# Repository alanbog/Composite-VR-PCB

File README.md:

# Composite-VR-PCB

This repository contains the hardware design of a controller board for CRT-based VR headset. The circuit contains an AMD Spartan 7 FPGA which splits the incoming HDMI video into separate luma only (black-and-white) NTSC composite video signals for the left and right eye. It also contains an RP2040 microcontroller which serves two purposes:

1. Act as a JTAG programmer for the FPGA using [xvc-pico](https://github.com/kholia/xvc-pico)
2. Transmit 3-DOF tracking data back to a PC using the on-board IMU (based on [Relativty](https://github.com/relativty/Relativty)).

The board also contains a USB hub and a USB C port intended to be connected to a Vive Tracker. When a Vive tracker is connected and SteamVR settings are configured to use the Vive Tracker to [override the default tracking](https://github.com/ValveSoftware/openvr/wiki/TrackingOverrides), the onboard IMU  tracking will not be used, and the RP2040 will only serve to let SteamVR know that the headset is connected. 

The board is the same dimensions and has the same mounting hole placement as a Raspberry Pi Zero.

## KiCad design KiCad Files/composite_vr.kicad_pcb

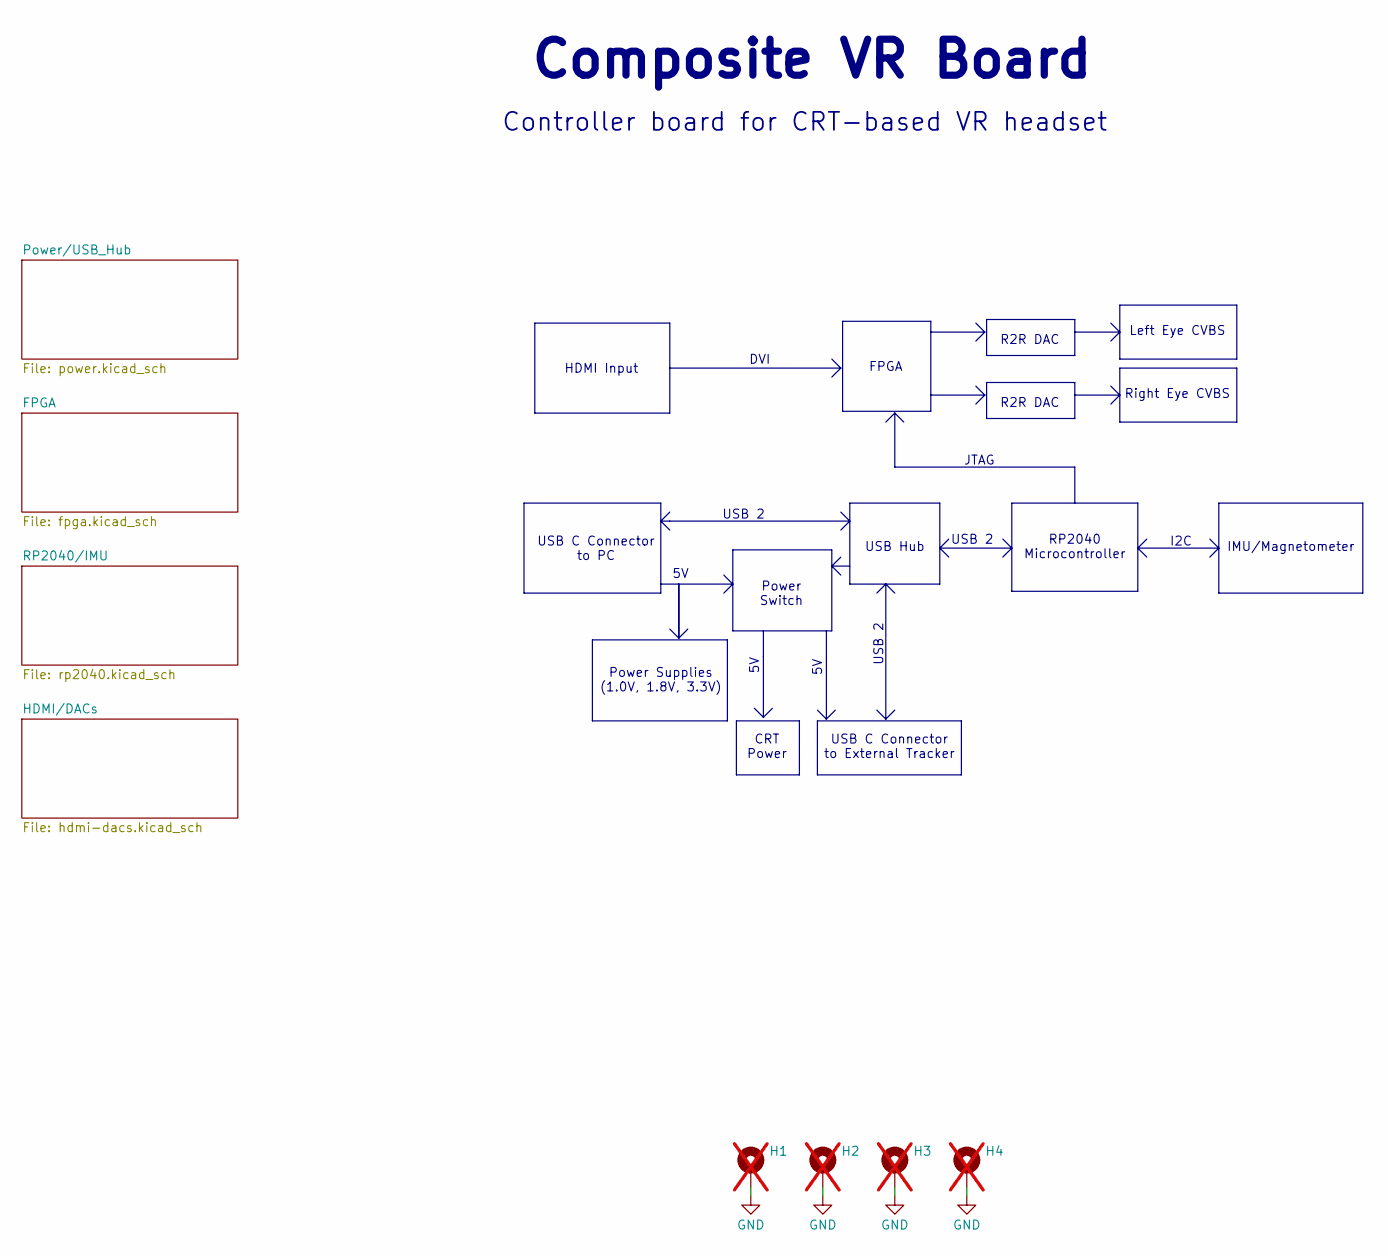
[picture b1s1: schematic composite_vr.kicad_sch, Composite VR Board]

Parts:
H1, H2, H3, H4: MountingHole_Pad; MountingHole_2.7mm_M2.5_DIN965_Pad; not fitted

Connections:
GND: H1.1, H2.1, H3.1, H4.1; also elsewhere on the board

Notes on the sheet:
USB 2
USB C Connector to External Tracker
Controller board for CRT-based VR headset
R2R DAC
FPGA
CRT Power
USB C Connector to PC
IMU/Magnetometer
Left Eye CVBS
USB Hub
Power Switch
Power Supplies (1.0V, 1.8V, 3.3V)
I2C
RP2040 Microcontroller
Right Eye CVBS
Composite VR Board
HDMI Input
DVI
JTAG

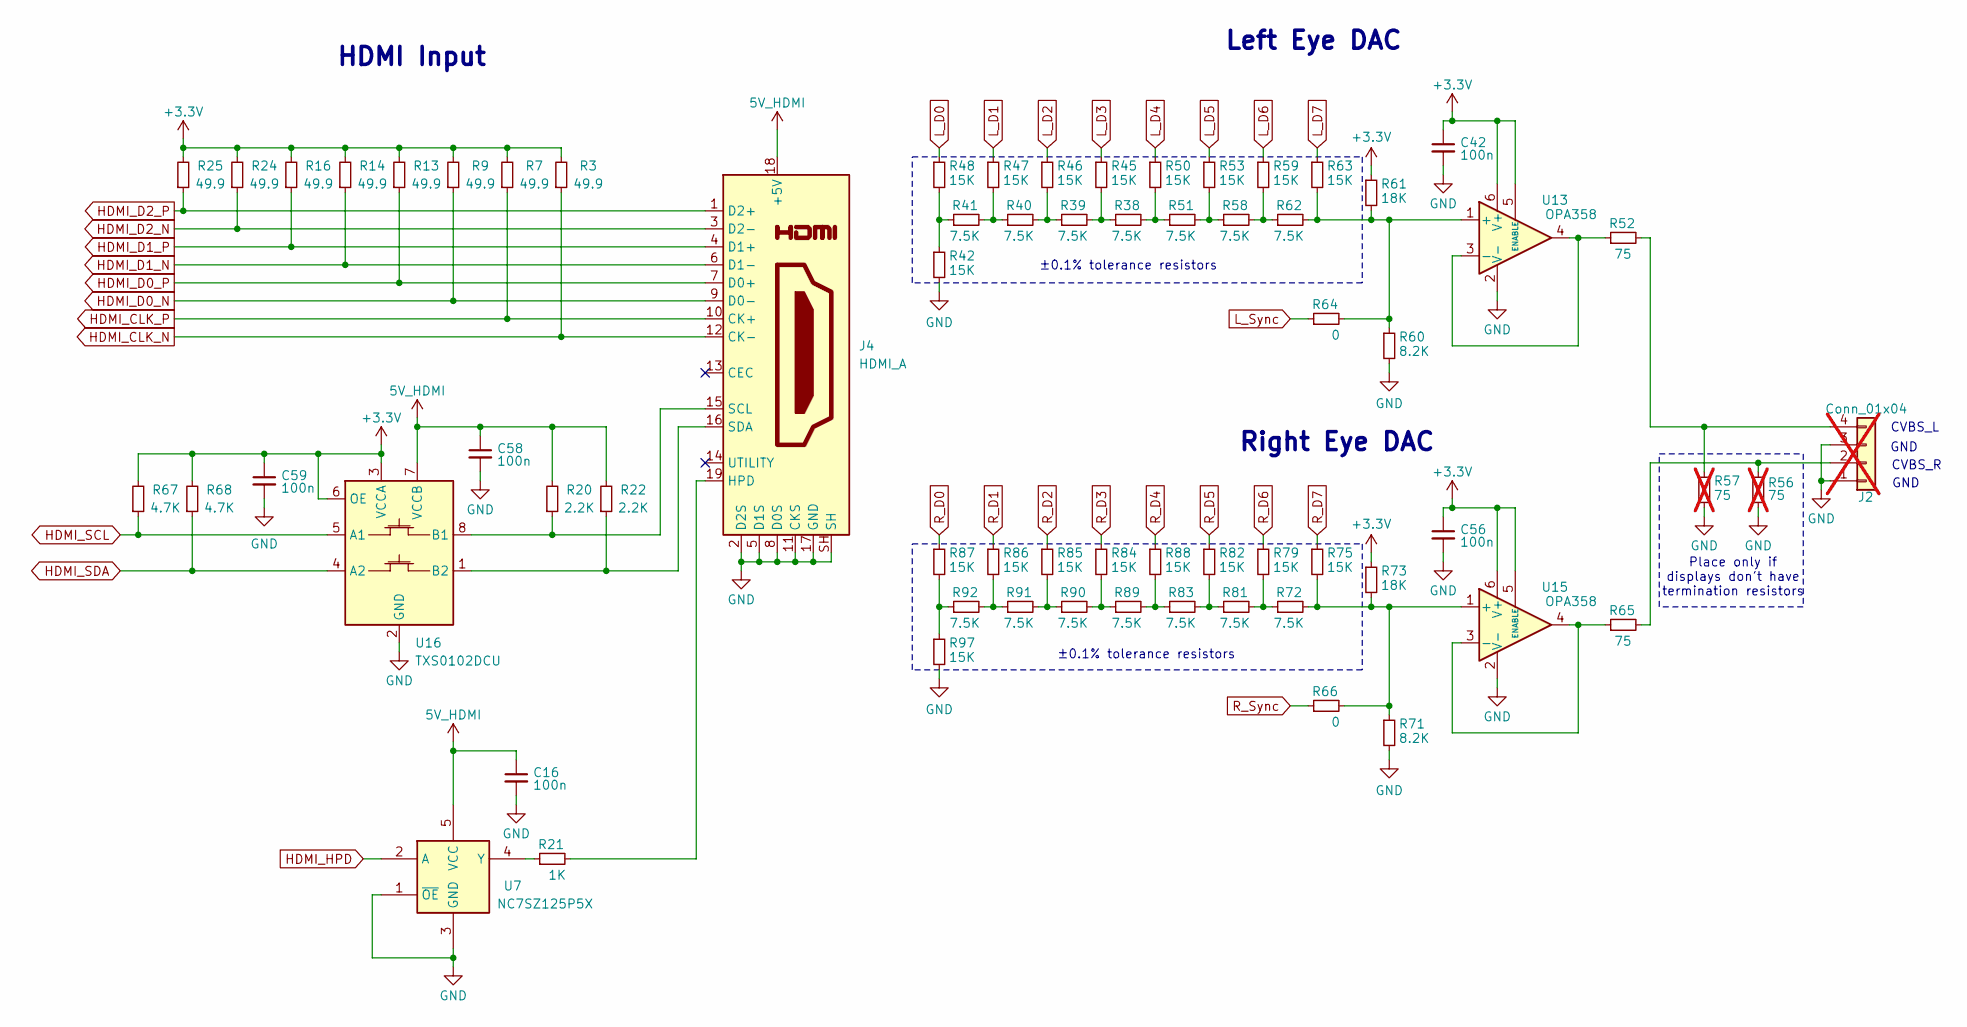
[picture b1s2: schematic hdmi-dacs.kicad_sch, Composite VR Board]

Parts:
C16, C42, C56, C58, C59: 100n; C_0402; Rating 16V; Tolerance 10%; Mfg PN CL05B104KO5NNNC; JLCPCB C1525
J2: Conn_01x04; PinHeader_1x04_P2.54mm_Vertical; not fitted
J4: HDMI_A; HDMI_A_Molex_208658-1001_Horizontal; Mfg PN HDMI-001S; JLCPCB C720616
R3, R7, R9, R13, R14, R16, R24, R25: 49.9; R_0402; Rating 62.5mW; Tolerance 1%; Mfg PN 0402WGF499JTCE; JLCPCB C25120
R20, R22: 2.2K; R_0402; Rating 62.5mW; Tolerance 1%; Mfg PN 0402WGF2201TCE; JLCPCB C25879
R21: 1K; R_0402; Rating 62.5mW; Tolerance 1%; Mfg PN 0402WGF1001TCE; JLCPCB C11702
R38, R39, R40, R41, R51, R58, R62, R72, R81, R83, R89, R90, R91, R92: 7.5K; R_0402; Rating 62.5mW; Tolerance 0.1%; Mfg PN TC0225B7501TCC; JLCPCB C28566374
R42, R45, R46, R47, R48, R50, R53, R59, R63, R75, R79, R82, R84, R85, R86, R87, R88, R97: 15K; R_0402; Rating 62.5mW; Tolerance 0.1%; Mfg PN TC02G1502BT; JLCPCB C20627044
R52, R65: 75; R_0402; Rating 62.5mW; Tolerance 1%; Mfg PN 0402WGF750JTCE; JLCPCB C25133
R56, R57: 75; R_0402; Rating 62.5mW; Tolerance 1%; Mfg PN 0402WGF750JTCE; JLCPCB C25133; not fitted
R60, R71: 8.2K; R_0402; Rating 62.5mW; Tolerance 1%; Mfg PN 0402WGF8201TCE; JLCPCB C25924
R61, R73: 18K; R_0402; Rating 62.5mW; Tolerance 1%; Mfg PN 0402WGF1802TCE; JLCPCB C25762
R64, R66: 0; R_0402; Rating 62.5mW; Tolerance 1%; Mfg PN 0402WGF0000TCE; JLCPCB C17168
R67, R68: 4.7K; R_0402; Rating 62.5mW; Tolerance 1%; Mfg PN 0402WGF4701TCE; JLCPCB C25900
U7: NC7SZ125P5X; SOT-353_SC-70-5; Mfg PN NC7SZ125P5X; JLCPCB C112084
U13, U15: OPA358; SOT-363_SC-70-6; Mfg PN OPA358AIDCKT; JLCPCB C2057755
U16: TXS0102DCU; VSSOP-8_2.3x2mm_P0.5mm; Mfg PN TXS0102DCUR; JLCPCB C53434

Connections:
5V_HDMI: C16.1, C58.1, J4.18 (+5V), R20.2, R22.2, U7.5 (VCC), U16.7 (VCCB)
+3.3V: C42.1, C56.1, C59.1, R3.2, R7.2, R9.2, R13.2, R14.2, R16.2, R24.2, R25.2, R61.1, R67.2, R68.2, R73.1, U13.5 (ENABLE), U13.6 (V+), U15.5 (ENABLE), U15.6 (V+), U16.3 (VCCA), U16.6 (OE); also elsewhere on the board
GND: C16.2, C42.2, C56.2, C58.2, C59.2, J2.1, J2.3, J4.2 (D2S), J4.5 (D1S), J4.8 (D0S), J4.11 (CKS), J4.17 (GND), J4.SH, R42.2, R56.2, R57.2, R60.2, R71.2, R97.2, U7.1 (~OE), U7.3 (GND), U13.2 (V-), U15.2 (V-), U16.2 (GND); also elsewhere on the board
HDMI_CLK_N: J4.12 (CK-), R3.1; also elsewhere on the board
HDMI_CLK_P: J4.10 (CK+), R7.1; also elsewhere on the board
HDMI_D0_N: J4.9 (D0-), R9.1; also elsewhere on the board
HDMI_D0_P: J4.7 (D0+), R13.1; also elsewhere on the board
HDMI_D1_N: J4.6 (D1-), R14.1; also elsewhere on the board
HDMI_D1_P: J4.4 (D1+), R16.1; also elsewhere on the board
HDMI_D2_N: J4.3 (D2-), R24.1; also elsewhere on the board
HDMI_D2_P: J4.1 (D2+), R25.1; also elsewhere on the board
HDMI_HPD: U7.2 (A); also elsewhere on the board
HDMI_SCL: R67.1, U16.5 (A1); also elsewhere on the board
HDMI_SDA: R68.1, U16.4 (A2); also elsewhere on the board
L_D0: R48.1; also elsewhere on the board
L_D1: R47.1; also elsewhere on the board
L_D2: R46.1; also elsewhere on the board
L_D3: R45.1; also elsewhere on the board
L_D4: R50.1; also elsewhere on the board
L_D5: R53.1; also elsewhere on the board
L_D6: R59.1; also elsewhere on the board
L_D7: R63.1; also elsewhere on the board
L_Sync: R64.1; also elsewhere on the board
unnamed: J2.2, R56.1, R65.2
unnamed: J2.4, R52.2, R57.1
unnamed: J4.19 (HPD), R21.2
unnamed: J4.15 (SCL), R20.1, U16.8 (B1)
unnamed: J4.16 (SDA), R22.1, U16.1 (B2)
unnamed: R38.1, R39.2, R45.2
unnamed: R38.2, R50.2, R51.1
unnamed: R39.1, R40.2, R46.2
unnamed: R40.1, R41.2, R47.2
unnamed: R41.1, R42.1, R48.2
unnamed: R51.2, R53.2, R58.1
unnamed: R58.2, R59.2, R62.1
unnamed: R72.1, R79.2, R81.2
unnamed: R81.1, R82.2, R83.2
unnamed: R83.1, R88.2, R89.2
unnamed: R84.2, R89.1, R90.2
unnamed: R85.2, R90.1, R91.2
unnamed: R86.2, R91.1, R92.2
unnamed: R87.2, R92.1, R97.1
unnamed: R21.1, U7.4 (Y)
unnamed: R60.1, R61.2, R62.2, R63.2, R64.2, U13.1 (+)
unnamed: R52.1, U13.3 (-), U13.4
unnamed: R66.2, R71.1, R72.2, R73.2, R75.2, U15.1 (+)
unnamed: R65.1, U15.3 (-), U15.4
R_D0: R87.1; also elsewhere on the board
R_D1: R86.1; also elsewhere on the board
R_D2: R85.1; also elsewhere on the board
R_D3: R84.1; also elsewhere on the board
R_D4: R88.1; also elsewhere on the board
R_D5: R82.1; also elsewhere on the board
R_D6: R79.1; also elsewhere on the board
R_D7: R75.1; also elsewhere on the board
R_Sync: R66.1; also elsewhere on the board

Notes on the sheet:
CVBS_R
CVBS_L
Right Eye DAC
±0.1% tolerance resistors
Place only if displays don't have termination resistors
GND
Left Eye DAC
HDMI Input

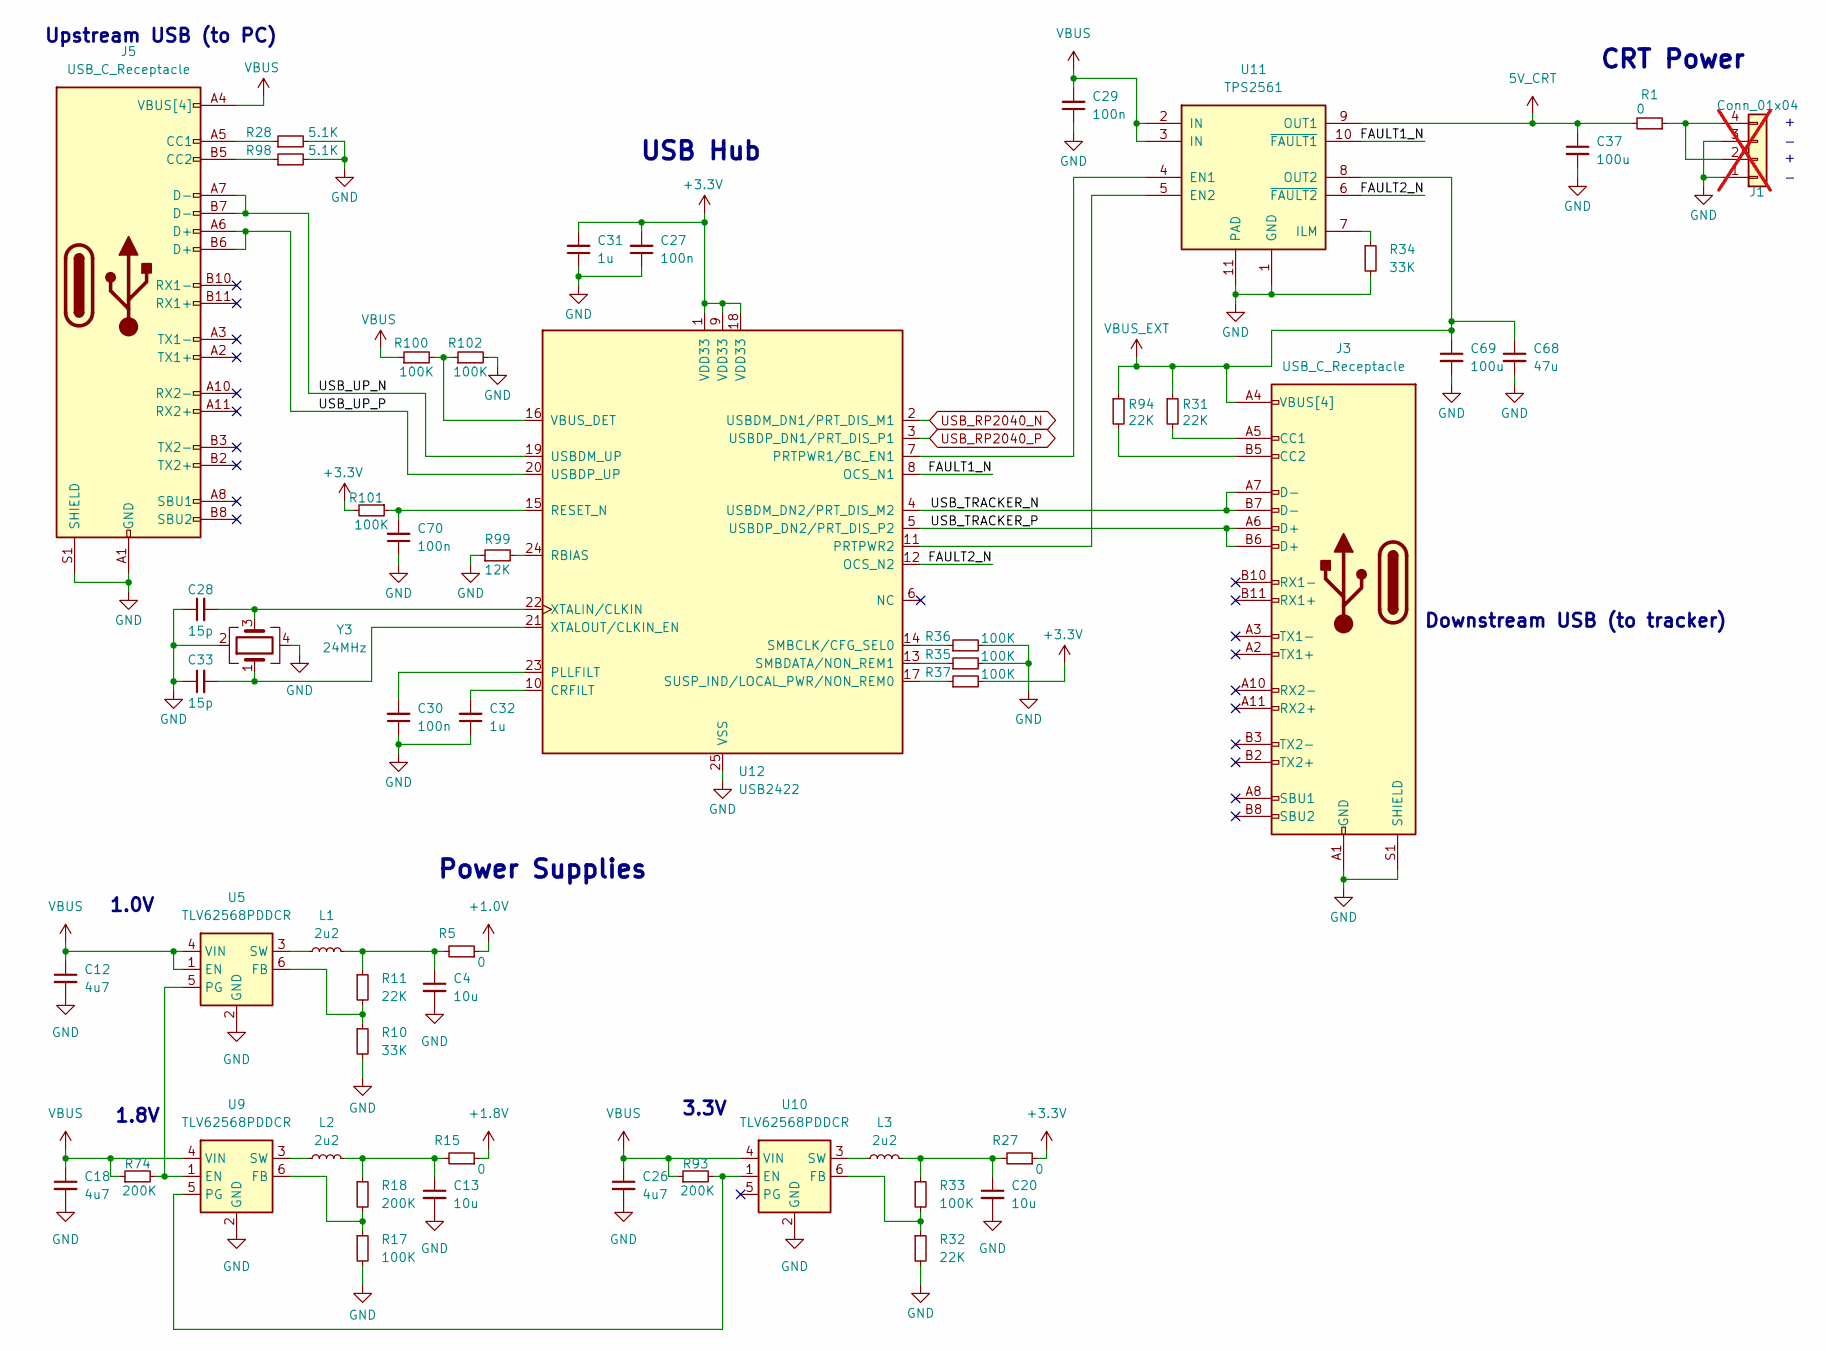
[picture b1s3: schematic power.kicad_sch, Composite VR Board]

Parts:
C4, C13, C20: 10u; C_0603; Rating 10V; Tolerance 10%; Mfg PN CL10A106KP8NNNC; JLCPCB C19702
C12, C18, C26: 4u7; C_0402; Rating 10V; Tolerance 20%; Mfg PN CL05A475MP5NRNC; JLCPCB C23733
C27, C29, C30, C70: 100n; C_0402; Rating 16V; Tolerance 10%; Mfg PN CL05B104KO5NNNC; JLCPCB C1525
C28, C33: 15p; C_0402; Rating 50V; Tolerance 5%; Mfg PN 0402CG150J500NT; JLCPCB C1548
C31, C32: 1u; C_0402; Rating 25V; Tolerance 10%; Mfg PN CL05A105KA5NQNC; JLCPCB C52923
C37, C69: 100u; C_1206; Rating 6.3V; Tolerance 20%; Mfg PN CL31A107MQHNNNE; JLCPCB C15008
C68: 47u; C_0805; Rating 6.3V; Tolerance 20%; Mfg PN CL21A476MQYNNNE; JLCPCB C16780
J1: Conn_01x04; PinHeader_1x04_P2.54mm_Vertical; not fitted
J3, J5: USB_C_Receptacle; USB_C_Receptacle_Molex_105450-0101; Mfg PN 1054500101; JLCPCB C134092
L1, L2, L3: 2u2; L_Taiyo-Yuden_MD-3030; Mfg PN LQH3NPN2R2MJRL; JLCPCB C341775
R1, R5, R15, R27: 0; R_0402; Rating 62.5mW; Tolerance 1%; Mfg PN 0402WGF0000TCE; JLCPCB C17168
R10, R34: 33K; R_0402; Rating 62.5mW; Tolerance 1%; Mfg PN 0402WGF3302TCE; JLCPCB C25779
R11, R31, R32, R94: 22K; R_0402; Rating 62.5mW; Tolerance 1%; Mfg PN 0402WGF2202TCE; JLCPCB C25768
R17, R33, R35, R36, R37, R100, R101, R102: 100K; R_0402; Rating 62.5mW; Tolerance 1%; Mfg PN 0402WGF1003TCE; JLCPCB C25741
R18, R74, R93: 200K; R_0402; Rating 62.5mW; Tolerance 1%; Mfg PN 0402WGF2003TCE; JLCPCB C25764
R28, R98: 5.1K; R_0402; Rating 62.5mW; Tolerance 1%; Mfg PN 0402WGF5101TCE; JLCPCB C25905
R99: 12K; R_0402; Rating 62.5mW; Tolerance 1%; Mfg PN 0402WGF1202TCE; JLCPCB C25752
U5, U9, U10: TLV62568PDDCR; SOT-23-6-small_courtyard; Mfg PN TLV62568PDDCR; JLCPCB C398369
U11: TPS2561; VSON-10-1EP_3x3mm_P0.5mm_EP1.65x2.4mm_ThermalVias; Mfg PN TPS2561DRCR; JLCPCB C140303
U12: USB2422; QFN-24-1EP_4x4mm_P0.5mm_EP2.5x2.5mm; Mfg PN USB2422T/MJ; JLCPCB C622611
Y3: 24MHz; Crystal_SMD_3225-4Pin_3.2x2.5mm; Mfg PN 7U24000E09UCG; JLCPCB C251611

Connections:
5V_CRT: C37.1, R1.2, U11.9 (OUT1)
+1.0V: R5.1; also elsewhere on the board
+1.8V: R15.1; also elsewhere on the board
+3.3V: C27.2, C31.2, R27.1, R37.2, R101.2, U12.1 (VDD33), U12.9 (VDD33), U12.18 (VDD33); also elsewhere on the board
/Power/USB_Hub/FAULT1_N: U11.10 (~FAULT1), U12.8 (OCS_N1)
/Power/USB_Hub/FAULT2_N: U11.6 (~FAULT2), U12.12 (OCS_N2)
/Power/USB_Hub/USB_TRACKER_N: J3.A7 (D-), J3.B7 (D-), U12.4 (USBDM_DN2/PRT_DIS_M2)
/Power/USB_Hub/USB_TRACKER_P: J3.A6 (D+), J3.B6 (D+), U12.5 (USBDP_DN2/PRT_DIS_P2)
/Power/USB_Hub/USB_UP_N: J5.A7 (D-), J5.B7 (D-), U12.19 (USBDM_UP)
/Power/USB_Hub/USB_UP_P: J5.A6 (D+), J5.B6 (D+), U12.20 (USBDP_UP)
GND: C4.2, C12.2, C13.2, C18.2, C20.2, C26.2, C27.1, C28.1, C29.1, C30.1, C31.1, C32.1, C33.1, C37.2, C68.2, C69.2, C70.1, J1.1, J1.3, J3.A1 (GND), J3.A12 (GND), J3.B1 (GND), J3.B12 (GND), J3.S1 (SHIELD), J5.A1 (GND), J5.A12 (GND), J5.B1 (GND), J5.B12 (GND), J5.S1 (SHIELD), R10.2, R17.2, R28.2, R32.2, R34.2, R35.2, R36.2, R98.2, R99.1, R102.2, U5.2 (GND), U9.2 (GND), U10.2 (GND), U11.1 (GND), U11.11 (PAD), U12.25 (VSS), Y3.2, Y3.4; also elsewhere on the board
unnamed: C4.1, L1.2, R5.2, R11.1
unnamed: C13.1, L2.2, R15.2, R18.1
unnamed: C20.1, L3.2, R27.2, R33.1
unnamed: J1.2, J1.4, R1.1
unnamed: J3.A5 (CC1), R31.2
unnamed: J3.B5 (CC2), R94.2
unnamed: J5.A5 (CC1), R28.1
unnamed: J5.B5 (CC2), R98.1
unnamed: R10.1, R11.2, U5.6 (FB)
unnamed: R74.2, U5.5 (PG), U9.1 (EN)
unnamed: L1.1, U5.3 (SW)
unnamed: R17.1, R18.2, U9.6 (FB)
unnamed: L2.1, U9.3 (SW)
unnamed: R93.2, U9.5 (PG), U10.1 (EN)
unnamed: R32.1, R33.2, U10.6 (FB)
unnamed: L3.1, U10.3 (SW)
unnamed: U11.4 (EN1), U12.7 (PRTPWR1/BC_EN1)
unnamed: U11.5 (EN2), U12.11 (PRTPWR2)
unnamed: R34.1, U11.7 (ILM)
unnamed: C32.2, U12.10 (CRFILT)
unnamed: C30.2, U12.23 (PLLFILT)
unnamed: R99.2, U12.24 (RBIAS)
unnamed: C70.2, R101.1, U12.15 (RESET_N)
unnamed: R36.1, U12.14 (SMBCLK/CFG_SEL0)
unnamed: R35.1, U12.13 (SMBDATA/NON_REM1)
unnamed: R37.1, U12.17 (SUSP_IND/LOCAL_PWR/NON_REM0)
unnamed: R100.2, R102.1, U12.16 (VBUS_DET)
unnamed: C28.2, U12.22 (XTALIN/CLKIN), Y3.3
unnamed: C33.2, U12.21 (XTALOUT/CLKIN_EN), Y3.1
USB_RP2040_N: U12.2 (USBDM_DN1/PRT_DIS_M1); also elsewhere on the board
USB_RP2040_P: U12.3 (USBDP_DN1/PRT_DIS_P1); also elsewhere on the board
VBUS: C12.1, C18.1, C26.1, C29.2, J5.A4 (VBUS[4]), J5.A9 (VBUS), J5.B4 (VBUS), J5.B9 (VBUS), R74.1, R93.1, R100.1, U5.1 (EN), U5.4 (VIN), U9.4 (VIN), U10.4 (VIN), U11.2 (IN), U11.3 (IN)
VBUS_EXT: C68.1, C69.1, J3.A4 (VBUS[4]), J3.A9 (VBUS), J3.B4 (VBUS), J3.B9 (VBUS), R31.1, R94.1, U11.8 (OUT2)

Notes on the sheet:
USB Hub
1.8V
Power Supplies
3.3V
CRT Power
1.0V
Upstream USB (to PC)
Downstream USB (to tracker)

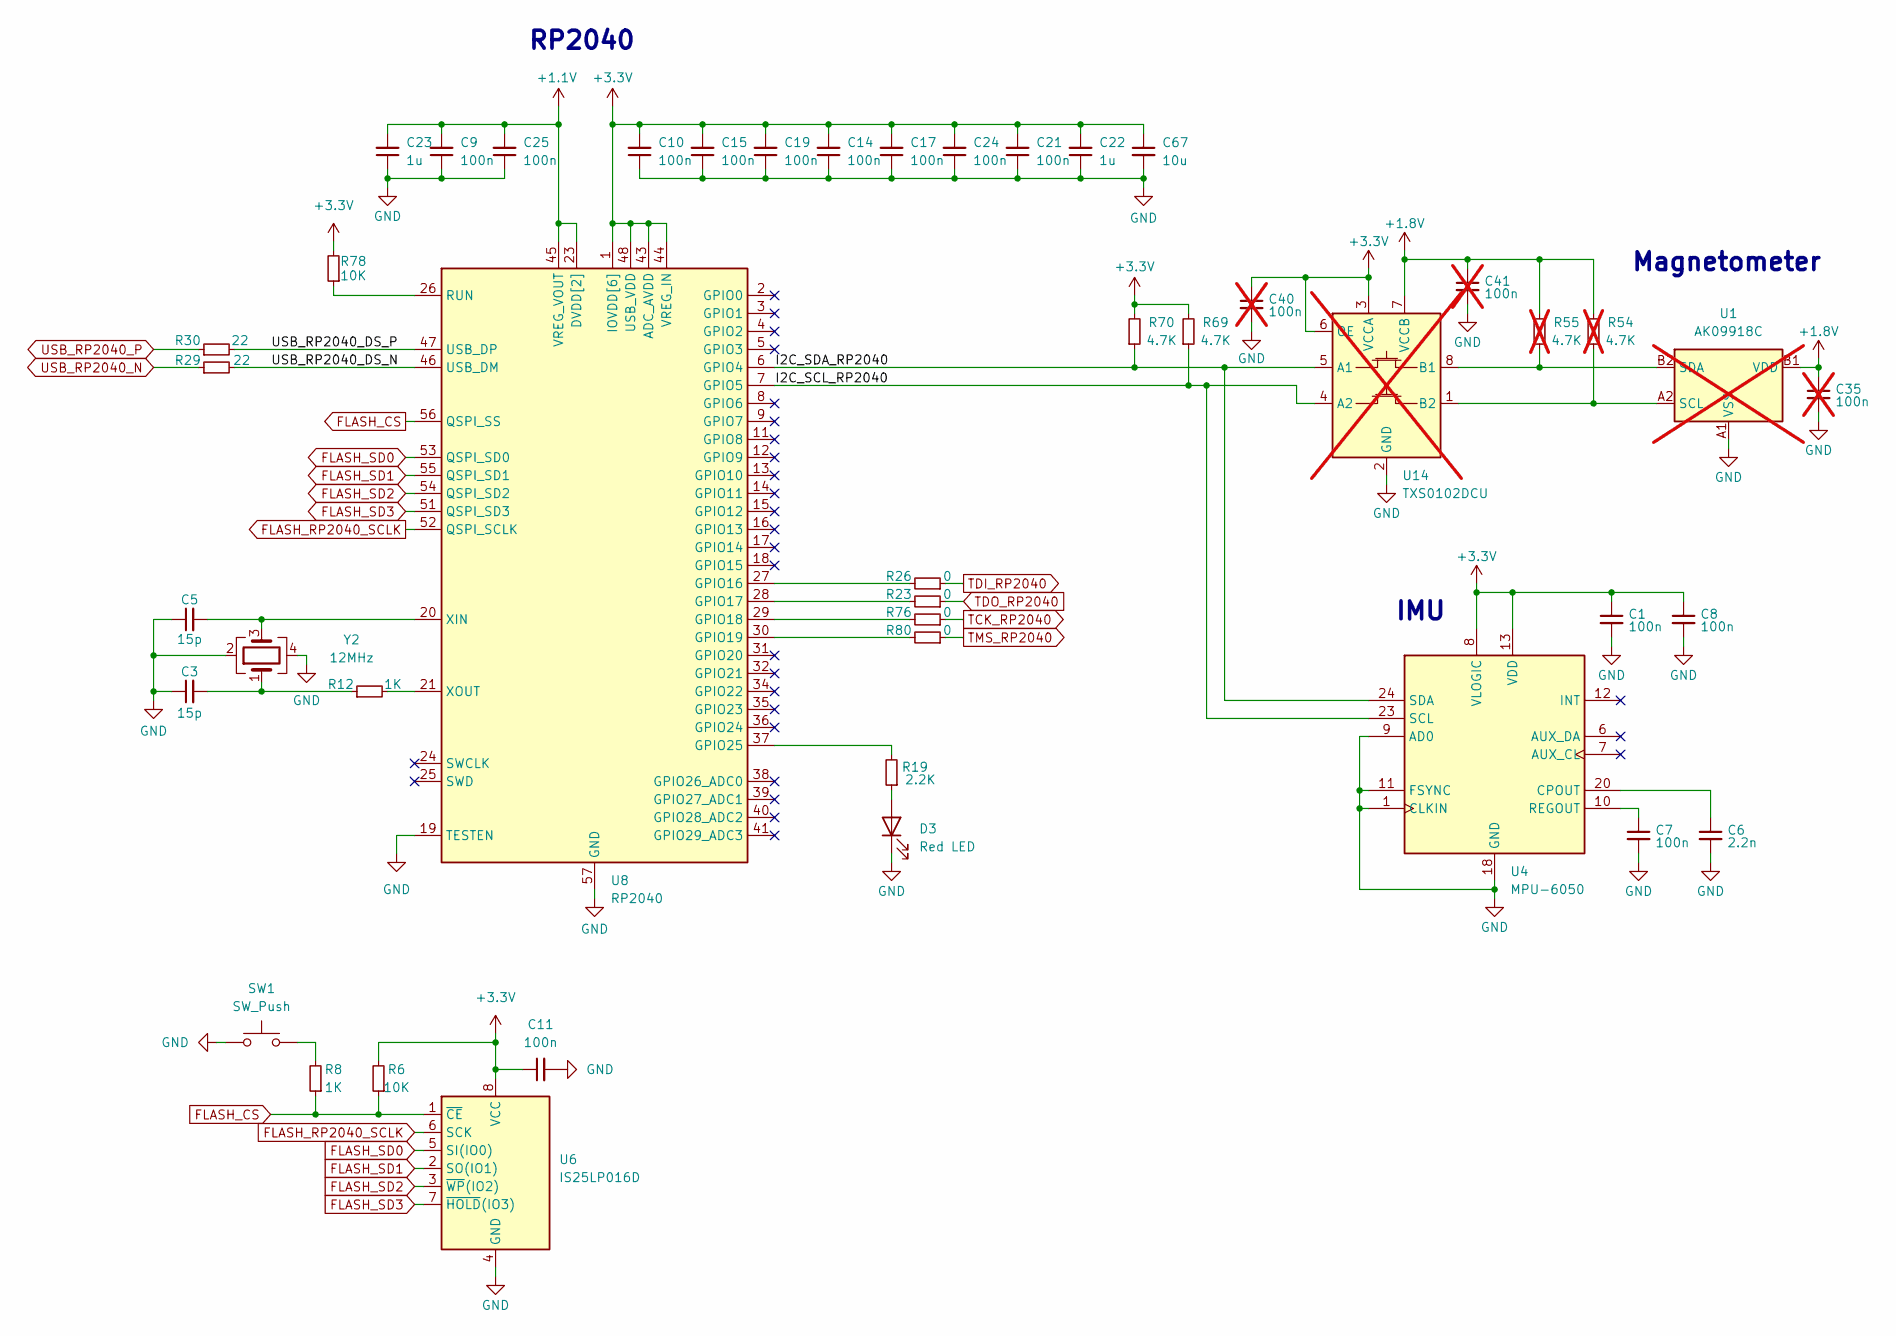
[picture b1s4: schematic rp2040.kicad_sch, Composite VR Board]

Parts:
C1, C7, C8, C9, C10, C11, C14, C15, C17, C19, C21, C24, C25: 100n; C_0402; Rating 16V; Tolerance 10%; Mfg PN CL05B104KO5NNNC; JLCPCB C1525
C3, C5: 15p; C_0402; Rating 50V; Tolerance 5%; Mfg PN 0402CG150J500NT; JLCPCB C1548
C6: 2.2n; C_0402; Rating 50V; Tolerance 10%; Mfg PN 0402B222K500NT; JLCPCB C1531
C22, C23: 1u; C_0402; Rating 25V; Tolerance 10%; Mfg PN CL05A105KA5NQNC; JLCPCB C52923
C35, C40, C41: 100n; C_0402; Rating 16V; Tolerance 10%; Mfg PN CL05B104KO5NNNC; JLCPCB C1525; not fitted
C67: 10u; C_0603; Rating 10V; Tolerance 10%; Mfg PN CL10A106KP8NNNC; JLCPCB C19702
D3: Red LED; LED_0603_1608Metric; Mfg PN KT-0603R; JLCPCB C2286
R6, R78: 10K; R_0402; Rating 62.5mW; Tolerance 1%; Mfg PN 0402WGF1002TCE; JLCPCB C25744
R8, R12: 1K; R_0402; Rating 62.5mW; Tolerance 1%; Mfg PN 0402WGF1001TCE; JLCPCB C11702
R19: 2.2K; R_0402; Rating 62.5mW; Tolerance 1%; Mfg PN 0402WGF2201TCE; JLCPCB C25879
R23, R26, R76, R80: 0; R_0402; Rating 62.5mW; Tolerance 1%; Mfg PN 0402WGF0000TCE; JLCPCB C17168
R29, R30: 22; R_0402; Rating 62.5mW; Tolerance 1%; Mfg PN 0402WGF220JTCE; JLCPCB C25092
R54, R55: 4.7K; R_0402; Rating 62.5mW; Tolerance 1%; Mfg PN 0402WGF4701TCE; JLCPCB C25900; not fitted
R69, R70: 4.7K; R_0402; Rating 62.5mW; Tolerance 1%; Mfg PN 0402WGF4701TCE; JLCPCB C25900
SW1: SW_Push; SW_SPST_TS-1088-xR025; Mfg PN TS-1088-AR02016; JLCPCB C720477
U1: AK09918C; WLP-4_0.83x0.83mm_P0.4mm; Mfg PN AK09918C; JLCPCB C2655004; not fitted
U4: MPU-6050; InvenSense_QFN-24_4x4mm_P0.5mm; Mfg PN MPU-6050; JLCPCB C24112
U6: IS25LP016D; SO-8_3.9x4.9mm_P1.27mm; Mfg PN IS25LP016D-JNLE-TR; JLCPCB C2653501
U8: RP2040; QFN-56-1EP_7x7mm_P0.4mm_EP3.2x3.2mm; Mfg PN RP2040; JLCPCB C2040
U14: TXS0102DCU; VSSOP-8_2.3x2mm_P0.5mm; Mfg PN TXS0102DCUR; JLCPCB C53434; not fitted
Y2: 12MHz; Crystal_SMD_3225-4Pin_3.2x2.5mm; Mfg PN 7U12000E09UCG; JLCPCB C524716

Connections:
+1.1V: C9.2, C23.2, C25.2, U8.23 (DVDD[2]), U8.45 (VREG_VOUT), U8.50 (DVDD)
+1.8V: C35.1, C41.1, R54.2, R55.2, U1.B1 (VDD), U14.7 (VCCB); also elsewhere on the board
+3.3V: C1.1, C8.1, C10.2, C11.1, C14.2, C15.2, C17.2, C19.2, C21.2, C22.2, C24.2, C40.1, C67.1, R6.2, R69.2, R70.2, R78.2, U4.8 (VLOGIC), U4.13 (VDD), U6.8 (VCC), U8.1 (IOVDD[6]), U8.10 (IOVDD), U8.22 (IOVDD), U8.33 (IOVDD), U8.42 (IOVDD), U8.43 (ADC_AVDD), U8.44 (VREG_IN), U8.48 (USB_VDD), U8.49 (IOVDD), U14.3 (VCCA), U14.6 (OE); also elsewhere on the board
/RP2040/IMU/I2C_SCL_RP2040: R69.1, U4.23 (SCL), U8.7 (GPIO5), U14.4 (A2)
/RP2040/IMU/I2C_SDA_RP2040: R70.1, U4.24 (SDA), U8.6 (GPIO4), U14.5 (A1)
/RP2040/IMU/USB_RP2040_DS_N: R29.2, U8.46 (USB_DM)
/RP2040/IMU/USB_RP2040_DS_P: R30.2, U8.47 (USB_DP)
FLASH_CS: R6.1, R8.1, U6.1 (~CE), U8.56 (QSPI_SS)
FLASH_RP2040_SCLK: U6.6 (SCK), U8.52 (QSPI_SCLK)
FLASH_SD0: U6.5 (SI(IO0)), U8.53 (QSPI_SD0)
FLASH_SD1: U6.2 (SO(IO1)), U8.55 (QSPI_SD1)
FLASH_SD2: U6.3 (~WP(IO2)), U8.54 (QSPI_SD2)
FLASH_SD3: U6.7 (~HOLD(IO3)), U8.51 (QSPI_SD3)
GND: C1.2, C3.1, C5.1, C6.2, C7.2, C8.2, C9.1, C10.1, C11.2, C14.1, C15.1, C17.1, C19.1, C21.1, C22.1, C23.1, C24.1, C25.1, C35.2, C40.2, C41.2, C67.2, D3.1 (K), SW1.1, U1.A1 (VSS), U4.1 (CLKIN), U4.9 (AD0), U4.11 (FSYNC), U4.18 (GND), U6.4 (GND), U8.19 (TESTEN), U8.57 (GND), U14.2 (GND), Y2.2, Y2.4; also elsewhere on the board
unnamed: C3.2, R12.1, Y2.1
unnamed: D3.2 (A), R19.1
unnamed: R8.2, SW1.2
unnamed: R54.1, U1.A2 (SCL), U14.1 (B2)
unnamed: R55.1, U1.B2 (SDA), U14.8 (B1)
unnamed: C6.1, U4.20 (CPOUT)
unnamed: C7.1, U4.10 (REGOUT)
unnamed: R26.2, U8.27 (GPIO16)
unnamed: R23.2, U8.28 (GPIO17)
unnamed: R76.2, U8.29 (GPIO18)
unnamed: R80.2, U8.30 (GPIO19)
unnamed: R19.2, U8.37 (GPIO25)
unnamed: R78.1, U8.26 (RUN)
unnamed: C5.2, U8.20 (XIN), Y2.3
unnamed: R12.2, U8.21 (XOUT)
TCK_RP2040: R76.1; also elsewhere on the board
TDI_RP2040: R26.1; also elsewhere on the board
TDO_RP2040: R23.1; also elsewhere on the board
TMS_RP2040: R80.1; also elsewhere on the board
USB_RP2040_N: R29.1; also elsewhere on the board
USB_RP2040_P: R30.1; also elsewhere on the board

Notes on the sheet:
IMU
Magnetometer
RP2040
